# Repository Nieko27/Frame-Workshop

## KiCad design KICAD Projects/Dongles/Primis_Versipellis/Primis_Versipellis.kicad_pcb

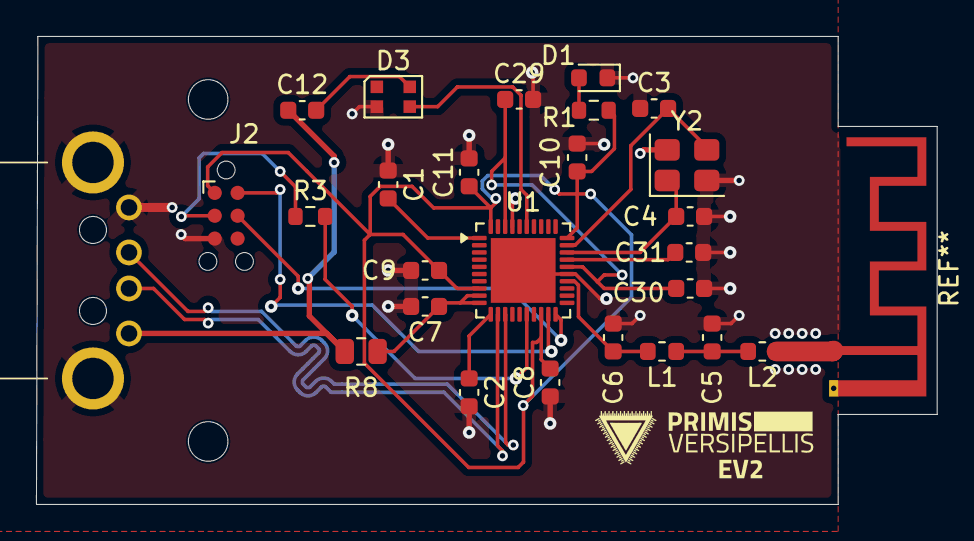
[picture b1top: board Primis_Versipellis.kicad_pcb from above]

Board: 2 copper layers, 50.0 x 26.0 mm, 28 parts (0 on the bottom side), 21 nets.

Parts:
C1, C8, C10, C12: 100nF; C_0603_1608Metric
C2, C7, C9: 4.7uF; C_0603_1608Metric
C3, C4: 12pF; C_0603_1608Metric
C5: 1.2pF; C_0603_1608Metric
C6: 1.0pF; C_0603_1608Metric
C11, C29: 1.0uF; C_0603_1608Metric
C30: N.C.; C_0603_1608Metric
C31: 100pF; C_0603_1608Metric
D1: LED; LED_0603_1608Metric
D3: WS2812B-2020; LED_WS2812B-2020_PLCC4_2.0x2.0mm
H1, H2: MountingHole; MountingHole_2.2mm_M2
J1: USB-05; USB05
J2: Conn_ARM_SWD_TagConnect_TC2030-NL; Tag-Connect_TC2030-IDC-NL_2x03_P1.27mm_Vertical
L1: 4.7nH; L_0603_1608Metric
L2: 2.2nH; L_0603_1608Metric
R1: 1.0k; R_0603_1608Metric
R3: 10k; R_0603_1608Metric
R8: 2R2; R_0805_2012Metric
U1: nRF52833_QDxx; QFN-40-1EP_5x5mm_P0.4mm_EP3.6x3.6mm
Y2: Crystal_GND24; Crystal_SMD_Abracon_ABM8G-4Pin_3.2x2.5mm

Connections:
D+: J1.2, U1.13 (D+)
D-: J1.3, U1.12 (D-)
DEC3: C31.1, U1.27 (DEC3)
DEC4_6: C29.1, C30.2, U1.26 (DEC6), U1.38 (DEC4)
GND: C1.1, C2.2, C3.1, C4.1, C5.1, C6.1, C7.2, C8.1, C9.2, C10.1, C11.2, C29.2, C30.1, C31.2, D1.1 (K), D3.2 (VSS), J1.1, J1.5, J1.6, J2.5 (GND), U1.25 (VSS_PA), U1.37 (VSS), U1.41 (VSS), Y2.2 (G), Y2.4 (G)
unnamed: C5.2, L1.1, L2.2
unnamed: D1.2 (A), R1.1
unnamed: D3.3 (DIN), U1.35 (AIN6/P0.30)
unnamed: C12.2, D3.4 (VDD)
unnamed: J2.4 (SWCLK), U1.20 (SWDCLK)
unnamed: J2.2 (SWDIO), U1.19 (SWDIO)
unnamed: J2.3 (~RESET), R3.1
unnamed: C6.2, L1.2, U1.24 (ANT)
unnamed: C1.2, U1.1 (DEC1)
unnamed: C2.1, U1.11 (DECUSB)
unnamed: R3.2, U1.16 (P0.18/~RESET)
unnamed: C7.1, R8.1, U1.9 (VDDH), U1.10 (VBUS)
unnamed: C4.2, U1.28 (XC1), Y2.1
unnamed: C3.2, U1.29 (XC2), Y2.3
VBUS: C12.1, J1.4, R8.2
VDD_nRF: C8.2, C9.1, C10.2, C11.1, J2.1 (VCC), R1.2, U1.8 (VDD), U1.18 (VDD), U1.30 (VDD), U1.40 (VDD)
